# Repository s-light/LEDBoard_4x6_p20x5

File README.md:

<!--lint disable maximum-line-length-->
<!--lint disable list-item-spacing-->
<!--lint disable list-item-indent-->

# LEDBoard_4x6_p20x5

- LEDBoard with 4x6 LEDs
- pixel pitch: 20mm x 5mm
- LED: [Rohm MSL0402RGB](https://www.rohm.com/datasheet/MSL0402RGBU) (1.8x1.6x0.5mm RGB)
- Driver: [TI TLC5971](http://www.ti.com/product/TLC5971) (16bit dimming, constant current driver)

<br>

<br>

<br>

---

<!-- TOC depthFrom:1 depthTo:6 withLinks:1 updateOnSave:1 orderedList:0 -->

- [LEDBoard_4x6_p20x5](#ledboard4x6p20x5)
	- [Project-Status](#project-status)
	- [Technical Information](#technical-information)
		- [mapping](#mapping)
			- [c++ / arduino](#c-arduino)
		- [HW](#hw)
		- [controlling](#controlling)
	- [License](#license)

<!-- /TOC -->

---
<br>

## Project-Status
WIP
- [x] design schematics
- [x] layout pcb
- [ ] order pcbs
- [ ] order parts
- [ ] solder boards
- [ ] test
- [ ] update documentation

## Technical Information
there are groups of 4 LEDs that are controlled by one TLC5971.  
every controller chip has 12 ConstantCurrent outputs.
so every LED is controllable individual.

### mapping
you need to create a mapping to linearize the order:  

TODO: test & check if this table is correct

|       | 0        | 1        | 2        | 3        |
| :---- | :------- | :------- | :------- | :------- |
| **0** | IC1 LED1 | IC1 LED2 | IC4 LED1 | IC4 LED2 |
| **1** | IC1 LED3 | IC1 LED4 | IC4 LED3 | IC4 LED4 |
| **2** | IC2 LED1 | IC2 LED2 | IC5 LED1 | IC5 LED2 |
| **3** | IC2 LED3 | IC2 LED4 | IC5 LED3 | IC5 LED4 |
| **4** | IC3 LED1 | IC3 LED2 | IC6 LED1 | IC6 LED2 |
| **5** | IC3 LED3 | IC3 LED4 | IC6 LED3 | IC6 LED4 |

#### c++ / arduino
```c++
const uint8_t channel_position_map[4][4] = {
    { 0,  1, 12, 13},
    { 2,  3, 14, 15},
    { 4,  5, 16, 17},
    { 6,  7, 18, 19},
    { 8,  9, 20, 21},
    {10, 11, 22, 23},
};
```

<!-- #### CircuitPython
```python
channel_position_map[4][4] = {
    { 0,  1, 12, 13},
    { 2,  3, 14, 15},
    { 4,  5, 16, 17},
    { 6,  7, 18, 19},
    { 8,  9, 20, 21},
    {10, 11, 22, 23},
};
``` -->

### HW
- PCB size: ?x?x1,6mm
- pixel-pitch: 20x5mm
- 3.8V..5.5V
- <= ??A (maximum)

### controlling
for arduino you can use [ulrichstern/Tlc59711](https://github.com/ulrichstern/Tlc59711)

for other things have a look at [LEDBoard_4x4_16bit](https://github.com/s-light/LEDBoard_4x4_16bit#controlling)

---

## License
<!-- license info -->
<p>

<br />
<span xmlns:dct="http://purl.org/dc/terms/" property="dct:title">
    all files in LEDBoard_4x6_p20x5
</span> by
<a xmlns:cc="http://creativecommons.org/ns#"
        href="https://github.com/s-light/LEDBoard_4x6_p20x5"
        property="cc:attributionName"
        rel="cc:attributionURL">
    Stefan Krüger (s-light)
</a>
are licensed under a<br/>
<a rel="license" href="http://creativecommons.org/licenses/by/4.0/">
    Creative Commons Attribution 4.0 International License
</a>.
</p>

all software parts/files are licensed under [MIT](LICENSE).

<!-- license info end -->

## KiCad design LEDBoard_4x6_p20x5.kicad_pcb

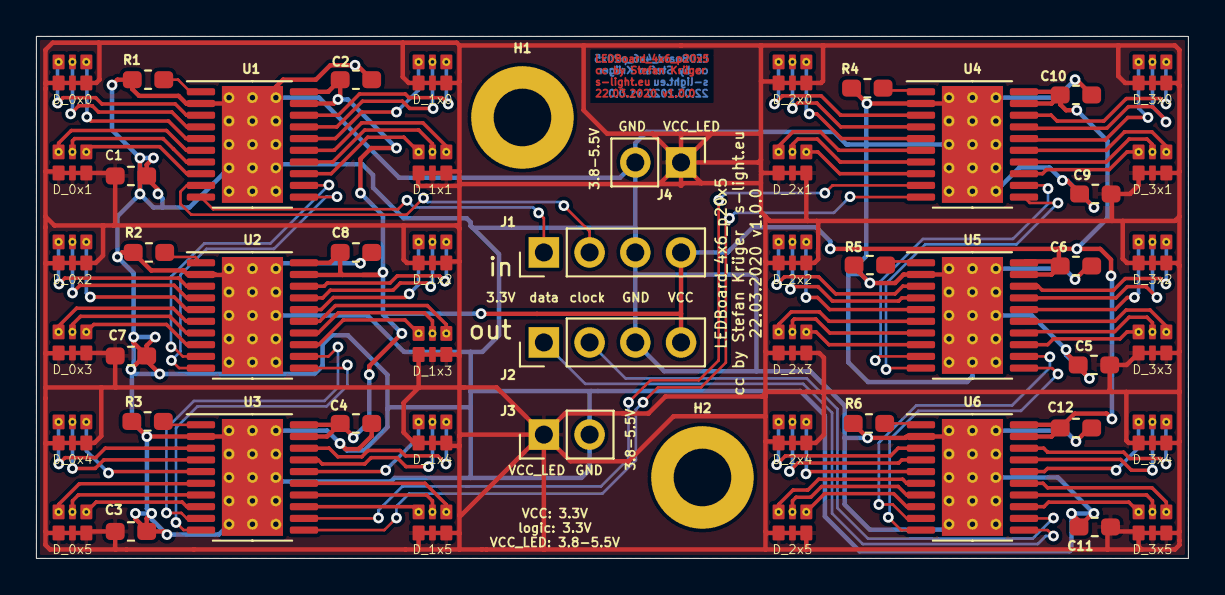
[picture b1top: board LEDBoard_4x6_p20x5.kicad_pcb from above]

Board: 2 copper layers, 64.0 x 29.0 mm, 54 parts (0 on the bottom side), 95 nets.

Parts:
C1, C3, C5, C7, C9, C11: 10uF 6.3V; C_0603_1608Metric_Pad1.05x0.95mm_HandSolder
C2, C4, C6, C8, C10, C12: 100n; C_0603_1608Metric_Pad1.05x0.95mm_HandSolder
D_0x0, D_0x1, D_0x2, D_0x3, D_0x4, D_0x5, D_1x0, D_1x1, D_1x2, D_1x3, D_1x4, D_1x5, D_2x0, D_2x1, D_2x2, D_2x3, D_2x4, D_2x5, D_3x0, D_3x1, D_3x2, D_3x3, D_3x4, D_3x5: LED_RGB; LED_RGB_0706_1816Metric_ROHM_ThermalVias
H1, H2: MH_M3; MountingHole_3.2mm_M3_ISO7380_Pad
J1: signal_in; PinHeader_1x04_P2.54mm_Vertical
J2: signal_out; PinHeader_1x04_P2.54mm_Vertical
J3: power_in; PinHeader_1x02_P2.54mm_Vertical
J4: power_out; PinHeader_1x02_P2.54mm_Vertical
R1, R2, R3, R4, R5, R6: 2k7 0.1%; R_0603_1608Metric_Pad1.05x0.95mm_HandSolder
U1, U2, U3, U4, U5, U6: TLC5971PWP; HTSSOP-20-1EP_4.4x6.5mm_P0.65mm_EP3.4x6.5mm_Mask2.75x3.43mm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

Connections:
/clock_1-2: U1.12, U2.9
/clock_2-3: U2.12, U3.9
/clock_3-4: U3.12, U4.9
/clock_4-5: U4.12, U5.9
/clock_5-6: U5.12, U6.9
/clock_in: J1.2, U1.9
/clock_out: J2.2, U6.12
/data_1-2: U1.11, U2.10
/data_2-3: U2.11, U3.10
/data_3-4: U3.11, U4.10
/data_4-5: U4.11, U5.10
/data_5-6: U5.11, U6.10
/data_in: J1.1, U1.10
/data_out: J2.1, U6.11
/led_0x0_b: D_0x0.3, U1.5
/led_0x0_g: D_0x0.2, U1.4
/led_0x0_r: D_0x0.1, U1.3
/led_0x1_b: D_0x1.3, U1.8
/led_0x1_g: D_0x1.2, U1.7
/led_0x1_r: D_0x1.1, U1.6
/led_0x2_b: D_0x2.3, U2.5
/led_0x2_g: D_0x2.2, U2.4
/led_0x2_r: D_0x2.1, U2.3
/led_0x3_b: D_0x3.3, U2.8
/led_0x3_g: D_0x3.2, U2.7
/led_0x3_r: D_0x3.1, U2.6
/led_0x4_b: D_0x4.3, U3.5
/led_0x4_g: D_0x4.2, U3.4
/led_0x4_r: D_0x4.1, U3.3
/led_0x5_b: D_0x5.3, U3.8
/led_0x5_g: D_0x5.2, U3.7
/led_0x5_r: D_0x5.1, U3.6
/led_1x0_b: D_1x0.3, U1.18
/led_1x0_g: D_1x0.2, U1.17
/led_1x0_r: D_1x0.1, U1.16
/led_1x1_b: D_1x1.3, U1.15
/led_1x1_g: D_1x1.2, U1.14
/led_1x1_r: D_1x1.1, U1.13
/led_1x2_b: D_1x2.3, U2.18
/led_1x2_g: D_1x2.2, U2.17
/led_1x2_r: D_1x2.1, U2.16
/led_1x3_b: D_1x3.3, U2.15
/led_1x3_g: D_1x3.2, U2.14
/led_1x3_r: D_1x3.1, U2.13
/led_1x4_b: D_1x4.3, U3.18
/led_1x4_g: D_1x4.2, U3.17
/led_1x4_r: D_1x4.1, U3.16
/led_1x5_b: D_1x5.3, U3.15
/led_1x5_g: D_1x5.2, U3.14
/led_1x5_r: D_1x5.1, U3.13
/led_2x0_b: D_2x0.3, U4.5
/led_2x0_g: D_2x0.2, U4.4
/led_2x0_r: D_2x0.1, U4.3
/led_2x1_b: D_2x1.3, U4.8
/led_2x1_g: D_2x1.2, U4.7
/led_2x1_r: D_2x1.1, U4.6
/led_2x2_b: D_2x2.3, U5.5
/led_2x2_g: D_2x2.2, U5.4
/led_2x2_r: D_2x2.1, U5.3
/led_2x3_b: D_2x3.3, U5.8
/led_2x3_g: D_2x3.2, U5.7
/led_2x3_r: D_2x3.1, U5.6
/led_2x4_b: D_2x4.3, U6.5
/led_2x4_g: D_2x4.2, U6.4
/led_2x4_r: D_2x4.1, U6.3
/led_2x5_b: D_2x5.3, U6.8
/led_2x5_g: D_2x5.2, U6.7
/led_2x5_r: D_2x5.1, U6.6
/led_3x0_b: D_3x0.3, U4.18
/led_3x0_g: D_3x0.2, U4.17
/led_3x0_r: D_3x0.1, U4.16
/led_3x1_b: D_3x1.3, U4.15
/led_3x1_g: D_3x1.2, U4.14
/led_3x1_r: D_3x1.1, U4.13
/led_3x2_b: D_3x2.3, U5.18
/led_3x2_g: D_3x2.2, U5.17
/led_3x2_r: D_3x2.1, U5.16
/led_3x3_b: D_3x3.3, U5.15
/led_3x3_g: D_3x3.2, U5.14
/led_3x3_r: D_3x3.1, U5.13
/led_3x4_b: D_3x4.3, U6.18
/led_3x4_g: D_3x4.2, U6.17
/led_3x4_r: D_3x4.1, U6.16
/led_3x5_b: D_3x5.3, U6.15
/led_3x5_g: D_3x5.2, U6.14
/led_3x5_r: D_3x5.1, U6.13
GND: C1.2, C2.2, C3.2, C4.2, C5.2, C6.2, C7.2, C8.2, C9.2, C10.2, C11.2, C12.2, H1.1, H2.1, J1.3, J2.3, J3.2, J4.2, R1.2, R2.2, R3.2, R4.2, R5.2, R6.2, U1.2, U1.21, U2.2, U2.21, U3.2, U3.21, U4.2, U4.21, U5.2, U5.21, U6.2, U6.21
unnamed: R1.1, U1.1
unnamed: R2.1, U2.1
unnamed: R3.1, U3.1
unnamed: R4.1, U4.1
unnamed: R5.1, U5.1
unnamed: R6.1, U6.1
VCC: C2.1, C4.1, C6.1, C8.1, C10.1, C12.1, J1.4, J2.4, U1.19, U1.20, U2.19, U2.20, U3.19, U3.20, U4.19, U4.20, U5.19, U5.20, U6.19, U6.20
VCC_LED: C1.1, C3.1, C5.1, C7.1, C9.1, C11.1, D_0x0.4, D_0x0.5, D_0x0.6, D_0x1.4, D_0x1.5, D_0x1.6, D_0x2.4, D_0x2.5, D_0x2.6, D_0x3.4, D_0x3.5, D_0x3.6, D_0x4.4, D_0x4.5, D_0x4.6, D_0x5.4, D_0x5.5, D_0x5.6, D_1x0.4, D_1x0.5, D_1x0.6, D_1x1.4, D_1x1.5, D_1x1.6, D_1x2.4, D_1x2.5, D_1x2.6, D_1x3.4, D_1x3.5, D_1x3.6, D_1x4.4, D_1x4.5, D_1x4.6, D_1x5.4, D_1x5.5, D_1x5.6, D_2x0.4, D_2x0.5, D_2x0.6, D_2x1.4, D_2x1.5, D_2x1.6, D_2x2.4, D_2x2.5, D_2x2.6, D_2x3.4, D_2x3.5, D_2x3.6, D_2x4.4, D_2x4.5, D_2x4.6, D_2x5.4, D_2x5.5, D_2x5.6, D_3x0.4, D_3x0.5, D_3x0.6, D_3x1.4, D_3x1.5, D_3x1.6, D_3x2.4, D_3x2.5, D_3x2.6, D_3x3.4, D_3x3.5, D_3x3.6, D_3x4.4, D_3x4.5, D_3x4.6, D_3x5.4, D_3x5.5, D_3x5.6, J3.1, J4.1

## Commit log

2020-03-16 prepare KiCad project
2020-03-16 start schematic
2020-03-17 schematic partly done
2020-03-18 fixed schematic ordering + placed parts
2020-03-20 pcb mostly done
2020-03-20 fixed image link
2020-03-21 added possible heatsink location
2020-03-21 pcb done
2020-03-22 export done
2020-03-22 exported gerber
2020-03-24 remove passmark + reexport
2020-03-25 export: added Excellon drill files

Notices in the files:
LEDBoard_4x6_p20x5.kicad_pcb:
cc by Stefan Krüger s-light.eu
